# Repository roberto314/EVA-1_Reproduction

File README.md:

# EVA-1_Reproduction

Recreation of the very rare K-K Systems EVA-1 Display Adapter for the Epson HX-20 Computer

In the folder disassembly are three versions of the original firmware:

* eva_orig: original firmware 
* eva_enh: enhanced firmware (mostly original)
* eva_ext: extended firmware (8k Text RAM, additional functions)
    - see the .asm file for more comments.

The gal folder contains the equations and .jed file for the GAL.

The monitor folder contains a modified version of Daniel Tufvesson's monitor. This is just for testing.

In the rom folder one can find the original rom and the font rom.

The schematics folder contains different versions of the reverse engineering process.

* EVA1: the original reverse engineered schematic and board (NOT FOR PRODUCTION!)
* EVA1_production: the mostly original EVA1 for production (DRAM does NOT work!)
* EVA86-2: from sources on the internet redrawn schematics of the EVA86 (not complete!)
* EVA1_v2: new version with SRAM as Graphic RAM, Arduino as mass storage and RP2040 for VGA Output.
* EVA1_Frontplatte: a drill template for the Strapubox 5003 case

For the newest Hardware Revision (0.5) use the File "disassembly/eva_ext/rom.bin" for a 28C64 or 27C64 ROM.

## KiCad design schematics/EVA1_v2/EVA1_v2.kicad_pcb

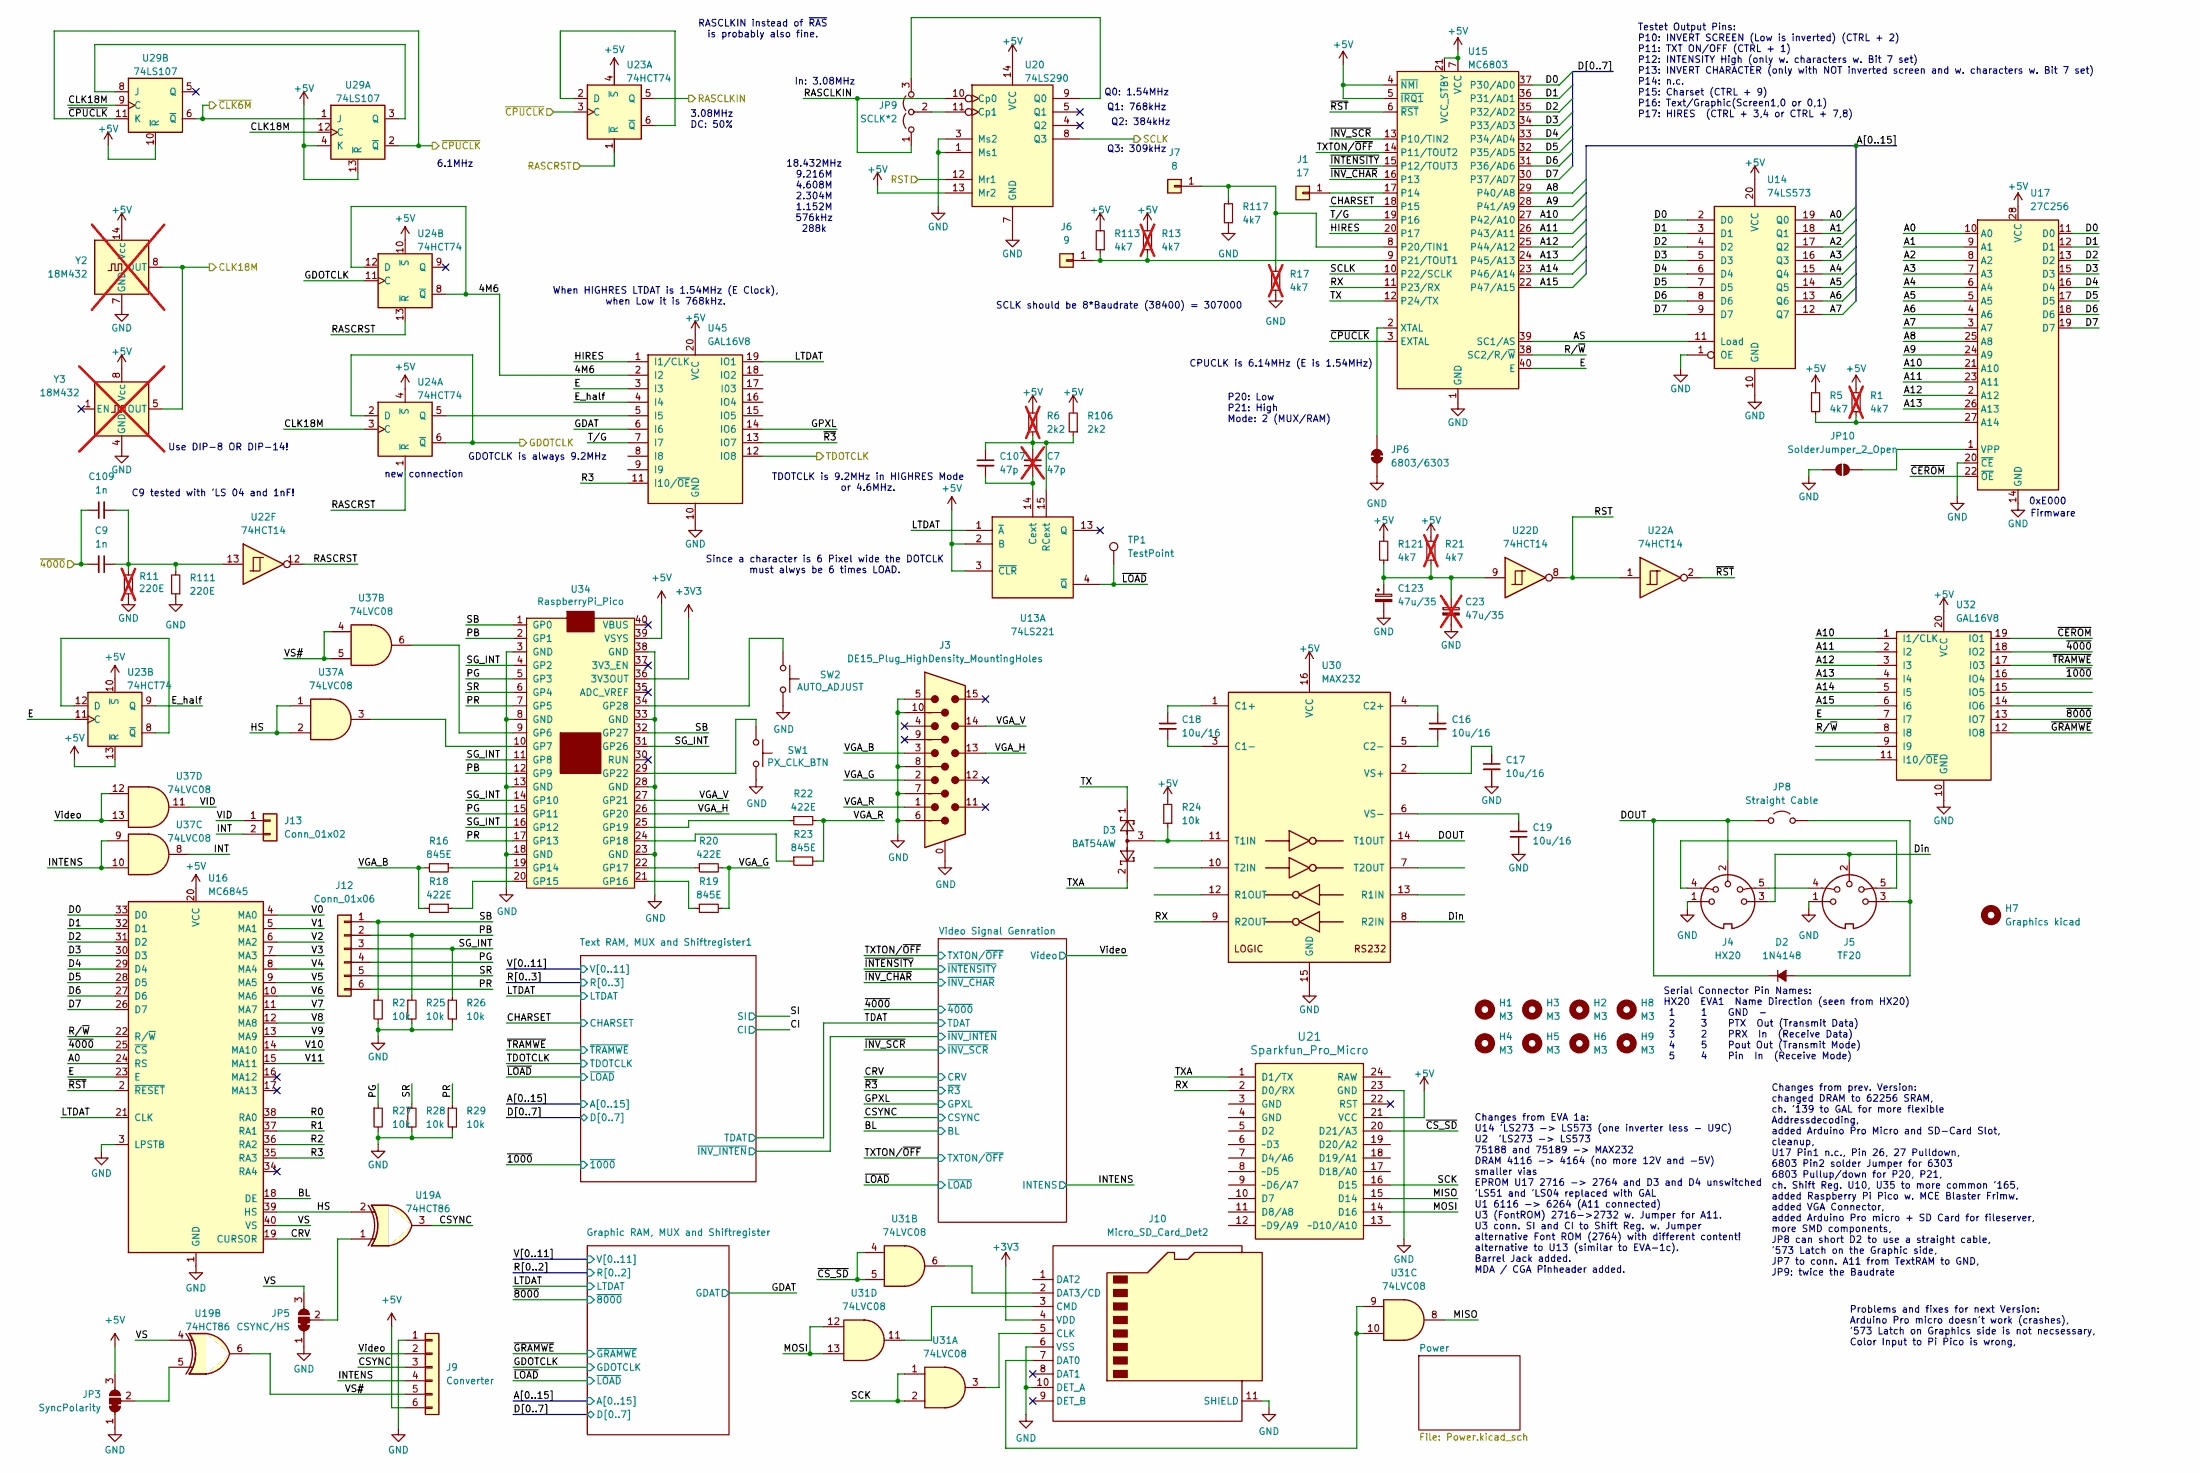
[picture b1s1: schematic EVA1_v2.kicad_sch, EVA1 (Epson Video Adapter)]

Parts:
C7: 47p; C_Disc_D4.7mm_W2.5mm_P5.00mm; not fitted
C9: 1n; C_Disc_D4.7mm_W2.5mm_P5.00mm
C16, C17, C18, C19: 10u/16; CP_Radial_D6.3mm_P2.50mm
C23: 47u/35; CP_Radial_D5.0mm_P2.50mm; not fitted
C107: 47p; C_1206_3216Metric_Pad1.33x1.80mm_HandSolder
C109: 1n; C_1206_3216Metric_Pad1.33x1.80mm_HandSolder
C123: 47u/35; CP_EIA-7343-31_Kemet-D_Pad2.25x2.55mm_HandSolder
D2: 1N4148; D_A-405_P7.62mm_Horizontal
D3: BAT54AW; SOT-23_Handsoldering
H1, H2, H3, H4, H5, H6, H8, H9: M3; MountingHole_3.2mm_M3
H7: Graphics kicad; KiCad-Logo2_6mm_SilkScreen
J1: 17; PinSocket_1x01_P2.54mm_Vertical
J3: DE15_Plug_HighDensity_MountingHoles; DSUB-15-HD_Female_Horizontal_P2.29x1.90mm_EdgePinOffset3.03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
J4: HX20; DIN-5_Stereo
J5: TF20; DIN-5_Stereo
J6: 9; PinSocket_1x01_P2.54mm_Vertical
J7: 8; PinSocket_1x01_P2.54mm_Vertical
J9: Converter; PinHeader_1x06_P2.54mm_Vertical
J10: Micro_SD_Card_Det2; microSD_HC_Hirose_DM3D-SF
J12: Conn_01x06; PinSocket_1x06_P2.54mm_Vertical
J13: Conn_01x02; PinSocket_1x02_P2.54mm_Vertical
JP3: SyncPolarity; SolderJumper-3_P1.3mm_Bridged12_RoundedPad1.0x1.5mm
JP5: CSYNC/HS; SolderJumper-3_P1.3mm_Bridged12_RoundedPad1.0x1.5mm
JP6: 6803/6303; SolderJumper-2_P1.3mm_Bridged_RoundedPad1.0x1.5mm
JP8: Straight Cable; PinHeader_1x02_P2.54mm_Vertical
JP9: SCLK*2; PinHeader_1x03_P2.54mm_Vertical
JP10: SolderJumper_2_Open; SolderJumper-2_P1.3mm_Open_RoundedPad1.0x1.5mm
R1, R13, R17, R21: 4k7; R_Axial_DIN0411_L9.9mm_D3.6mm_P12.70mm_Horizontal; not fitted
R2, R24, R25, R26, R27, R28, R29: 10k; R_1206_3216Metric_Pad1.30x1.75mm_HandSolder
R5, R113, R117, R121: 4k7; R_1206_3216Metric_Pad1.30x1.75mm_HandSolder
R6: 2k2; R_Axial_DIN0411_L9.9mm_D3.6mm_P12.70mm_Horizontal; not fitted
R11: 220E; R_Axial_DIN0411_L9.9mm_D3.6mm_P12.70mm_Horizontal; not fitted
R16, R19, R23: 845E; R_1206_3216Metric_Pad1.30x1.75mm_HandSolder
R18, R20, R22: 422E; R_1206_3216Metric_Pad1.30x1.75mm_HandSolder
R106: 2k2; R_1206_3216Metric_Pad1.30x1.75mm_HandSolder
R111: 220E; R_1206_3216Metric_Pad1.30x1.75mm_HandSolder
SW1: PX_CLK_BTN; SW_Tactile_SPST_Angled_PTS645Vx83-2LFS
SW2: AUTO_ADJUST; SW_Tactile_SPST_Angled_PTS645Vx83-2LFS
TP1: TestPoint; TestPoint_Loop_D1.80mm_Drill1.0mm_Beaded
U13: 74LS221; DIP-16_W7.62mm
U14: 74LS573; DIP-20_W7.62mm
U15: MC6803; DIP-40_W15.24mm_Socket
U16: MC6845; DIP-40_W15.24mm_Socket
U17: 27C256; DIP-28_W15.24mm
U19: 74HCT86; DIP-14_W7.62mm
U20: 74LS290; DIP-14_W7.62mm
U21: Sparkfun_Pro_Micro
U22: 74HCT14; DIP-14_W7.62mm
U23, U24: 74HCT74; DIP-14_W7.62mm
U29: 74LS107; DIP-14_W7.62mm
U30: MAX232; DIP-16_W7.62mm_Socket
U31, U37: 74LVC08; SOIC-14_3.9x8.7mm_P1.27mm
U32, U45: GAL16V8; DIP-20_W7.62mm
U34: RaspberryPi_Pico; raspberry_pi_pico
Y2: 18M432; Oscillator_DIP-14; not fitted
Y3: 18M432; Oscillator_DIP-8; not fitted

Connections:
+3V3: J10.4 (VDD), U34.36 (3V3OUT); also elsewhere on the board
+5V: J9.6, JP3.3 (B), R1.1, R5.1, R6.2, R13.2, R21.2, R24.2, R106.2, R113.2, R121.2, U13.2 (B), U13.3 (~CLR), U14.20 (VCC), U15.4 (~NMI), U15.5 (~IRQ1), U15.7 (VCC), U15.21 (VCC_STBY), U16.20 (VCC), U17.28 (VCC), U20.13 (Mr2), U20.14 (VCC), U21.21 (VCC), U23.4 (~S), U23.10 (~S), U23.13 (~R), U24.4 (~S), U24.10 (~S), U29.4 (K), U29.10 (~R), U29.13 (~R), U30.16 (VCC), U32.20 (VCC), U34.39 (VSYS), U45.20 (VCC), Y2.14 (Vcc), Y3.8 (Vcc); also elsewhere on the board
/4M6: U24.8 (~Q), U24.12 (D), U45.2 (I2)
/A0: U14.19 (Q0), U16.24 (RS), U17.10 (A0); also elsewhere on the board
/A1: U14.18 (Q1), U17.9 (A1); also elsewhere on the board
/A2: U14.17 (Q2), U17.8 (A2); also elsewhere on the board
/A3: U14.16 (Q3), U17.7 (A3); also elsewhere on the board
/A4: U14.15 (Q4), U17.6 (A4); also elsewhere on the board
/A5: U14.14 (Q5), U17.5 (A5); also elsewhere on the board
/A6: U14.13 (Q6), U17.4 (A6); also elsewhere on the board
/A7: U14.12 (Q7), U17.3 (A7); also elsewhere on the board
/A8: U15.29 (P40/A8), U17.25 (A8); also elsewhere on the board
/A9: U15.28 (P41/A9), U17.24 (A9); also elsewhere on the board
/A10: U15.27 (P42/A10), U17.21 (A10), U32.1 (I1/CLK); also elsewhere on the board
/A11: U15.26 (P43/A11), U17.23 (A11), U32.2 (I2); also elsewhere on the board
/A12: U15.25 (P44/A12), U17.2 (A12), U32.3 (I3); also elsewhere on the board
/A13: U15.24 (P45/A13), U17.26 (A13), U32.4 (I4); also elsewhere on the board
/A14: U15.23 (P46/A14), U32.5 (I5); also elsewhere on the board
/A15: U15.22 (P47/A15), U32.6 (I6)
/AS: U14.11 (Load), U15.39 (SC1/AS)
/BL: U16.18 (DE); also elsewhere on the board
/CHARSET: U15.18 (P15); also elsewhere on the board
/CLK18M: U24.3 (C), U29.9 (C), U29.12 (C), Y2.8 (OUT), Y3.5 (OUT)
/CRV: U16.19 (CURSOR); also elsewhere on the board
/CSYNC: J9.3, U19.3; also elsewhere on the board
/D0: U14.2 (D0), U15.37 (P30/AD0), U16.33 (D0), U17.11 (D0); also elsewhere on the board
/D1: U14.3 (D1), U15.36 (P31/AD1), U16.32 (D1), U17.12 (D1); also elsewhere on the board
/D2: U14.4 (D2), U15.35 (P32/AD2), U16.31 (D2), U17.13 (D2); also elsewhere on the board
/D3: U14.5 (D3), U15.34 (P33/AD3), U16.30 (D3), U17.15 (D3); also elsewhere on the board
/D4: U14.6 (D4), U15.33 (P34/AD4), U16.29 (D4), U17.16 (D4); also elsewhere on the board
/D5: U14.7 (D5), U15.32 (P35/AD5), U16.28 (D5), U17.17 (D5); also elsewhere on the board
/D6: U14.8 (D6), U15.31 (P36/AD6), U16.27 (D6), U17.18 (D6); also elsewhere on the board
/D7: U14.9 (D7), U15.30 (P37/AD7), U16.26 (D7), U17.19 (D7); also elsewhere on the board
/DOUT: D2.1 (K), J4.2, JP8.1 (A), U30.14 (T1OUT)
/Din: J4.3, J5.2, U30.8 (R2IN)
/E: U15.40 (E), U16.23 (E), U23.11 (C), U32.7 (I7), U45.3 (I3)
/E_half: U23.9 (Q), U45.4 (I4)
/GDAT: U45.6 (I6); also elsewhere on the board
/GDOTCLK: U24.2 (D), U24.6 (~Q), U24.11 (C); also elsewhere on the board
/GPXL: U45.14 (IO6); also elsewhere on the board
/HIRES: U15.20 (P17), U45.1 (I1/CLK)
/HS: U16.39 (HS), U19.2, U37.1, U37.2
/INT: J13.2, U37.8
/INTENS: J9.4, U37.9, U37.10; also elsewhere on the board
/LTDAT: U13.1 (~A), U16.21 (CLK), U45.19 (IO1); also elsewhere on the board
/MISO: U21.15 (D14), U31.8
/MOSI: U21.14 (D16), U31.12, U31.13
/PB: J12.2, R25.1, U34.2 (GP1), U34.12 (GP9)
/PG: J12.4, R27.1, U34.5 (GP3), U34.15 (GP11)
/PR: J12.6, R29.1, U34.7 (GP5), U34.17 (GP13)
/R0: U16.38 (RA0); also elsewhere on the board
/R1: U16.37 (RA1); also elsewhere on the board
/R2: U16.36 (RA2); also elsewhere on the board
/R3: U16.35 (RA3), U45.11 (I10/~OE); also elsewhere on the board
/RASCLKIN: JP9.1 (A), U20.10 (Cp0), U23.5 (Q)
/RASCRST: U22.12, U23.1 (~R), U24.1 (~R), U24.13 (~R)
/RST: U20.12 (Mr1), U22.1, U22.8
/RX: U15.11 (P23/RX), U21.2 (D0/RX), U30.9 (R2OUT)
/R/~W: U15.38 (SC2/R/~W), U16.22 (R/~W), U32.8 (I8)
/SB: J12.1, R2.1, U34.1 (GP0), U34.32 (GP27)
/SCK: U21.16 (D15), U31.1, U31.2
/SCLK: U15.10 (P22/SCLK), U20.8 (Q3)
/SG_INT: J12.3, R26.1, U34.4 (GP2), U34.11 (GP8), U34.14 (GP10), U34.16 (GP12), U34.31 (GP26)
/SR: J12.5, R28.1, U34.6 (GP4)
/TDOTCLK: U45.12 (IO8); also elsewhere on the board
/TX: D3.1, U15.12 (P24/TX)
/TXA: D3.2, U21.1 (D1/TX)
/TXTON/~OFF: U15.14 (P11/TOUT2); also elsewhere on the board
/V0: U16.4 (MA0); also elsewhere on the board
/V1: U16.5 (MA1); also elsewhere on the board
/V2: U16.6 (MA2); also elsewhere on the board
/V3: U16.7 (MA3); also elsewhere on the board
/V4: U16.8 (MA4); also elsewhere on the board
/V5: U16.9 (MA5); also elsewhere on the board
/V6: U16.10 (MA6); also elsewhere on the board
/V7: U16.11 (MA7); also elsewhere on the board
/V8: U16.12 (MA8); also elsewhere on the board
/V9: U16.13 (MA9); also elsewhere on the board
/V10: U16.14 (MA10); also elsewhere on the board
/V11: U16.15 (MA11); also elsewhere on the board
/VGA_B: J3.3, R16.2, R18.2
/VGA_G: J3.2, R19.2, R20.2
/VGA_H: J3.13, U34.26 (GP20)
/VGA_R: J3.1, R22.2, R23.2
/VGA_V: J3.14, U34.27 (GP21)
/VID: J13.1, U37.11
/VS: JP5.3 (B), U16.40 (VS), U19.4
/VS#: J9.5, U19.6, U37.4, U37.5
/Video: J9.2, U37.12, U37.13; also elsewhere on the board
/~1000: U32.16 (IO4); also elsewhere on the board
/~4000: C9.2, C109.1, U16.25 (~CS), U32.18 (IO2)
/~8000: U32.13 (IO7); also elsewhere on the board
/~CEROM: U17.22 (~OE), U32.19 (IO1)
/~CLK6M: U29.1 (J), U29.6 (~Q)
/~CPUCLK: U15.3 (EXTAL), U23.3 (C), U29.2 (~Q), U29.11 (K)
/~CS_SD: U21.20 (D21/A3), U31.4, U31.5
/~GRAMWE: U32.12 (IO8); also elsewhere on the board
/~INTENSITY: U15.15 (P12/TOUT3); also elsewhere on the board
/~INV_CHAR: U15.16 (P13); also elsewhere on the board
/~INV_SCR: U15.13 (P10/TIN2); also elsewhere on the board
/~LOAD: TP1.1, U13.4 (~Q); also elsewhere on the board
/~R3: U45.13 (IO7); also elsewhere on the board
/~RST: U15.6 (~RST), U16.2 (~RESET), U22.2
/~TRAMWE: U32.17 (I03); also elsewhere on the board
GND: C17.2, C19.2, C23.2, C123.2, J3.0, J3.5, J3.6, J3.7, J3.8, J3.10, J4.1, J5.1, J9.1, J10.6 (VSS), J10.10 (DET_A), J10.11 (SHIELD), JP3.1 (A), JP5.1 (A), JP6.1 (A), JP10.1 (A), R2.2, R11.1, R17.1, R25.2, R26.2, R27.2, R28.2, R29.2, R111.1, R117.1, SW1.2, SW2.2, U14.1 (OE), U14.10 (GND), U15.1 (GND), U16.1 (GND), U16.3 (LPSTB), U17.14 (GND), U17.20 (~CE), U20.1 (Ms1), U20.3 (Ms2), U20.7 (GND), U21.23 (GND), U30.15 (GND), U32.10 (GND), U34.3 (GND), U34.8 (GND), U34.13 (GND), U34.18 (GND), U34.23 (GND), U34.28 (GND), U34.33 (GND), U34.38 (GND), U45.10 (GND), Y2.7 (GND), Y3.4 (GND); also elsewhere on the board
unnamed: C9.1, C109.2, R11.2, R111.2, U22.13
unnamed: C23.1, C123.1, R21.1, R121.1, U22.9
unnamed: D2.2 (A), J5.3, JP8.2 (B)
unnamed: J1.1, U15.17 (P14)
unnamed: J4.4, J5.5
unnamed: J4.5, J5.4
unnamed: J6.1, R13.1, R113.1, U15.9 (P21/TOUT1)
unnamed: J7.1, R17.2, R117.2, U15.8 (P20/TIN1)
unnamed: J10.5 (CLK), U31.3
unnamed: J10.3 (CMD), U31.11
unnamed: J10.7 (DAT0), U31.9, U31.10
unnamed: J10.2 (DAT3/CD), U31.6
unnamed: JP3.2 (C), U19.5
unnamed: JP5.2 (C), U19.1
unnamed: JP6.2 (B), U15.2 (XTAL)
unnamed: JP9.3 (B), U20.9 (Q0)
unnamed: JP9.2 (C), U20.11 (Cp1)
unnamed: JP10.2 (B), U17.1 (VPP)
unnamed: C7.1, C107.2, U13.14 (Cext)
unnamed: C7.2, C107.1, R6.1, R106.1, U13.15 (RCext)
unnamed: R1.2, R5.2, U17.27 (A14)
unnamed: U23.2 (D), U23.6 (~Q)
unnamed: U23.8 (~Q), U23.12 (D)
unnamed: U24.5 (Q), U45.5 (I5)
unnamed: U29.3 (Q), U29.8 (J)
unnamed: C18.1, U30.1 (C1+)
unnamed: C18.2, U30.3 (C1-)
unnamed: C16.1, U30.4 (C2+)
unnamed: C16.2, U30.5 (C2-)
unnamed: D3.3, R24.1, U30.11 (T1IN)
unnamed: C17.1, U30.2 (VS+)
unnamed: C19.1, U30.6 (VS-)
unnamed: U34.9 (GP6), U37.6
unnamed: U34.10 (GP7), U37.3
unnamed: R16.1, U34.19 (GP14)
unnamed: R18.1, U34.20 (GP15)
unnamed: R19.1, U34.21 (GP16)
unnamed: R20.1, U34.22 (GP17)
unnamed: R23.1, U34.24 (GP18)
unnamed: R22.1, U34.25 (GP19)
unnamed: SW1.1, U34.29 (GP22)
unnamed: SW2.1, U34.34 (GP28)

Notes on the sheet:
P20: Low P21: High Mode: 2 (MUX/RAM)
3.08MHz DC: 50%
TDOTCLK is 9.2MHz in HIGHRES Mode or 4.6MHz.
Testet Output Pins: P10: INVERT SCREEN (Low is inverted) (CTRL + 2) P11: TXT ON/OFF (CTRL + 1) P12: INTENSITY High (only w. characters w. Bit 7 set) P13: INVERT CHARACTER (only with NOT inverted screen and w. characters w. Bit 7 set) P14: n.c. P15: Charset (CTRL + 9) P16: Text/Graphic(Screen1,0 or 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
RASCLKIN instead of ~{RAS} is probably also fine.
Use DIP-8 OR DIP-14!
GDOTCLK is always 9.2MHz
C9 tested with 'LS 04 and 1nF!
Q1: 768kHz
CPUCLK is 6.14MHz (E is 1.54MHz)
Serial Connector Pin Names: HX20 EVA1 Name Direction (seen from HX20) 1 1 GND - 2 3 PTX Out (Transmit Data) 3 2 PRX In (Receive Data) 4 5 Pout Out (Transmit Mode) 5 4 Pin In (Receive Mode)
Q3: 309kHz
Changes from EVA 1a: U14 'LS273 -> LS573 (one inverter less - U9C) U2 'LS273 -> LS573 75188 and 75189 -> MAX232 DRAM 4116 -> 4164 (no more 12V and -5V) smaller vias EPROM U17 2716 -> 2764 and D3 and D4 unswitched 'LS51 and 'LS04 replaced with GAL U1 6116 -> 6264 (A11 connected) U3 (FontROM) 2716->2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
SCLK should be 8*Baudrate (38400) = 307000
When HIGHRES LTDAT is 1.54MHz (E Clock), when Low it is 768kHz.
6.1MHz
Since a character is 6 Pixel wide the DOTCLK must alwys be 6 times LOAD.
Firmware
18.432MHz 9.216M 4.608M 2.304M 1.152M 576kHz 288k
new connection
0xE000
Q0: 1.54MHz
In: 3.08MHz
Q2: 384kHz
Changes from prev. Version: changed DRAM to 62256 SRAM, ch. '139 to GAL for more flexible Addressdecoding, added Arduino Pro Micro and SD-Card Slot, cleanup, U17 Pin1 n.c., Pin 26, 27 Pulldown, 6803 Pin2 solder Jumper for 6303 6803 Pullup/down for P20, P21, ch. Shift Reg. U10, U35 to more common '1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
Problems and fixes for next Version: Arduino Pro micro doesn't work (crashes), '573 Latch on Graphics side is not necsessary, Color Input to Pi Pico is wrong,

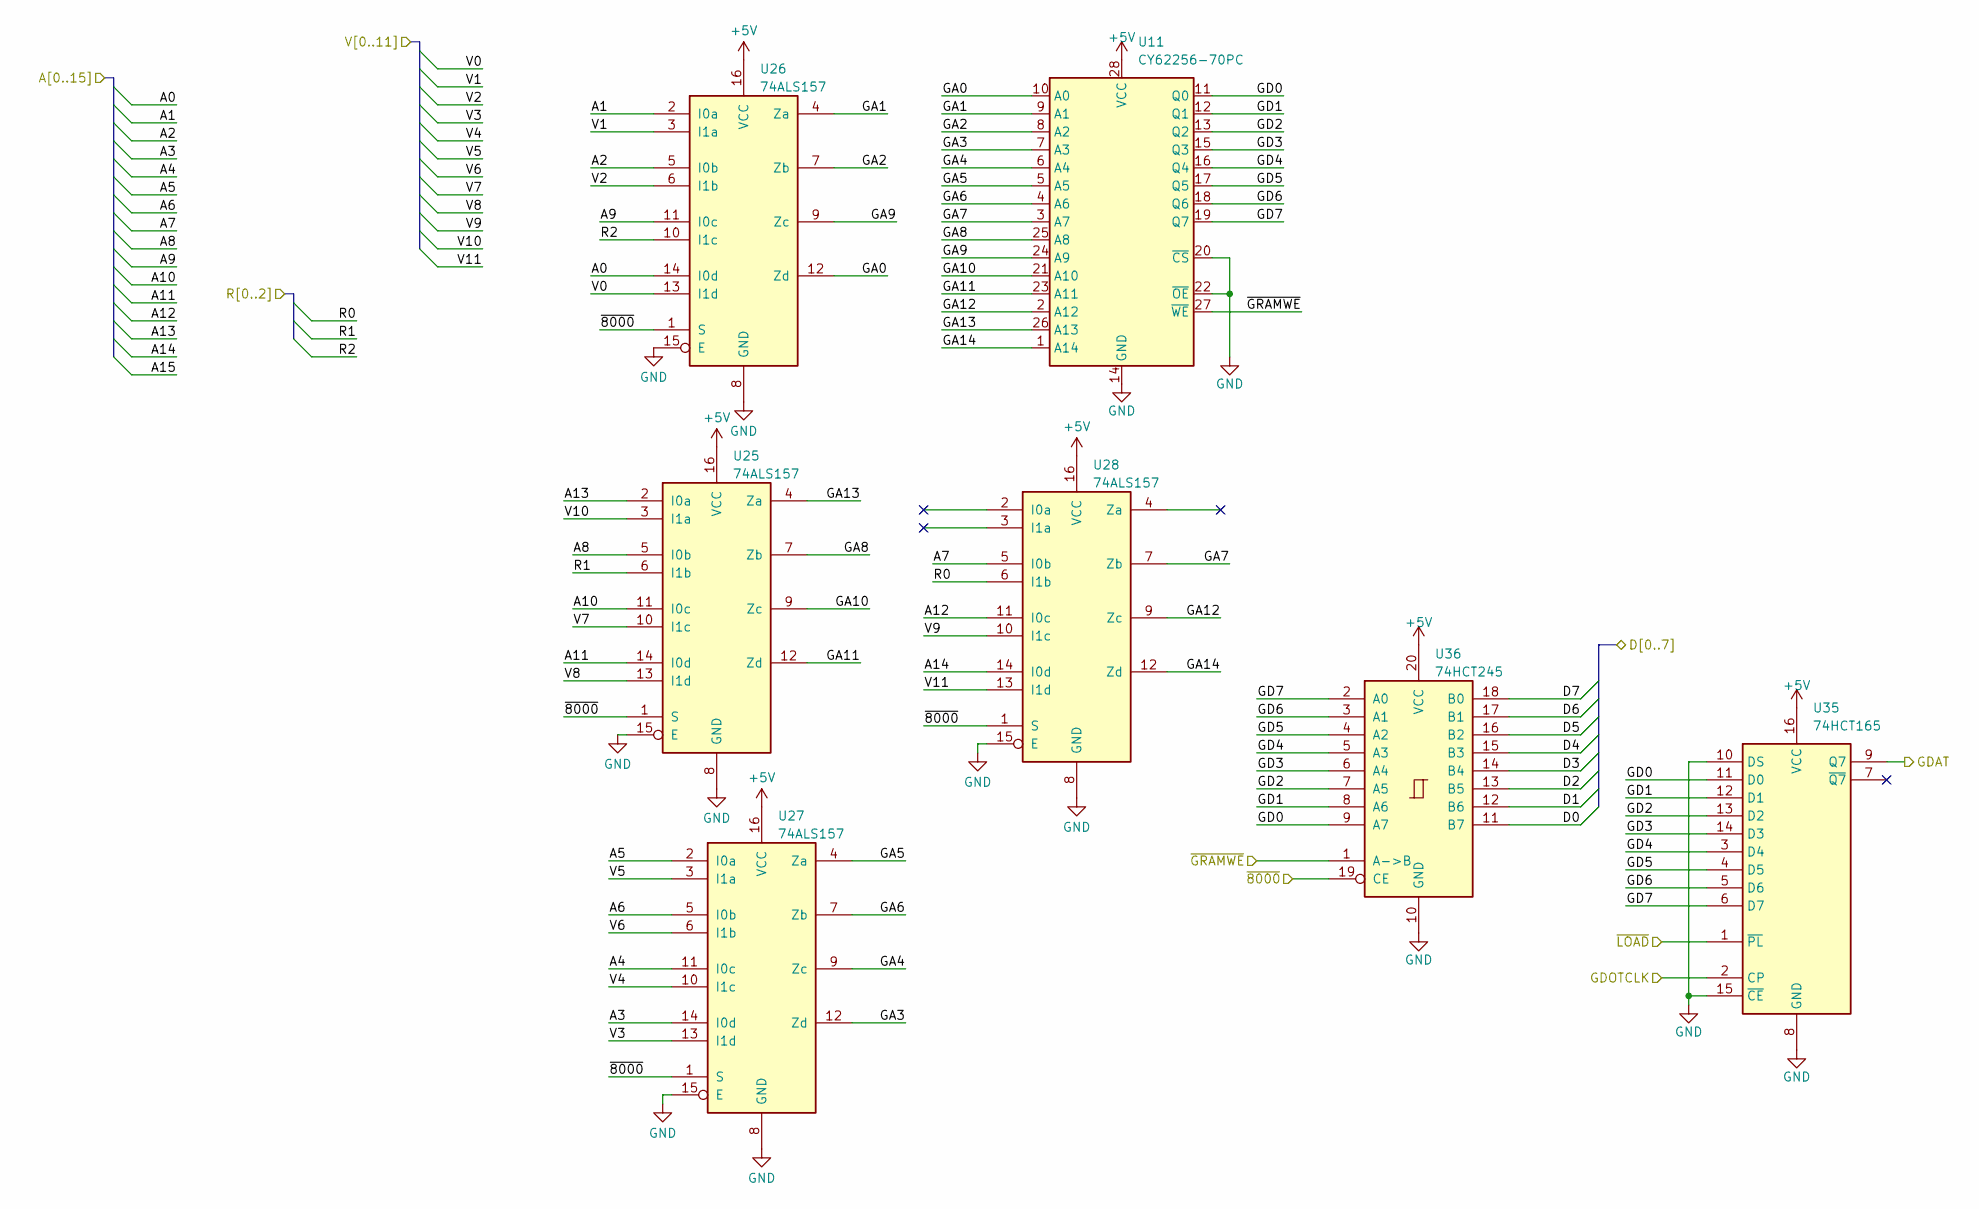
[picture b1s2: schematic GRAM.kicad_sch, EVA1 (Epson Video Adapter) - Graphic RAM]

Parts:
U11: CY62256-70PC; DIP-28_W15.24mm
U25, U26, U27, U28: 74ALS157; DIP-16_W7.62mm
U35: 74HCT165; DIP-16_W7.62mm_Socket
U36: 74HCT245; DIP-20_W7.62mm

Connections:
+5V: U11.28 (VCC), U25.16 (VCC), U26.16 (VCC), U27.16 (VCC), U28.16 (VCC), U35.16 (VCC), U36.20 (VCC); also elsewhere on the board
/A0: U26.14 (I0d); also elsewhere on the board
/A1: U26.2 (I0a); also elsewhere on the board
/A2: U26.5 (I0b); also elsewhere on the board
/A3: U27.14 (I0d); also elsewhere on the board
/A4: U27.11 (I0c); also elsewhere on the board
/A5: U27.2 (I0a); also elsewhere on the board
/A6: U27.5 (I0b); also elsewhere on the board
/A7: U28.5 (I0b); also elsewhere on the board
/A8: U25.5 (I0b); also elsewhere on the board
/A9: U26.11 (I0c); also elsewhere on the board
/A10: U25.11 (I0c); also elsewhere on the board
/A11: U25.14 (I0d); also elsewhere on the board
/A12: U28.11 (I0c); also elsewhere on the board
/A13: U25.2 (I0a); also elsewhere on the board
/A14: U28.14 (I0d); also elsewhere on the board
/D0: U36.11 (B7); also elsewhere on the board
/D1: U36.12 (B6); also elsewhere on the board
/D2: U36.13 (B5); also elsewhere on the board
/D3: U36.14 (B4); also elsewhere on the board
/D4: U36.15 (B3); also elsewhere on the board
/D5: U36.16 (B2); also elsewhere on the board
/D6: U36.17 (B1); also elsewhere on the board
/D7: U36.18 (B0); also elsewhere on the board
/GDAT: U35.9 (Q7); also elsewhere on the board
/GDOTCLK: U35.2 (CP); also elsewhere on the board
/Graphic RAM, MUX and Shiftregister/GA0: U11.10 (A0), U26.12 (Zd)
/Graphic RAM, MUX and Shiftregister/GA1: U11.9 (A1), U26.4 (Za)
/Graphic RAM, MUX and Shiftregister/GA2: U11.8 (A2), U26.7 (Zb)
/Graphic RAM, MUX and Shiftregister/GA3: U11.7 (A3), U27.12 (Zd)
/Graphic RAM, MUX and Shiftregister/GA4: U11.6 (A4), U27.9 (Zc)
/Graphic RAM, MUX and Shiftregister/GA5: U11.5 (A5), U27.4 (Za)
/Graphic RAM, MUX and Shiftregister/GA6: U11.4 (A6), U27.7 (Zb)
/Graphic RAM, MUX and Shiftregister/GA7: U11.3 (A7), U28.7 (Zb)
/Graphic RAM, MUX and Shiftregister/GA8: U11.25 (A8), U25.7 (Zb)
/Graphic RAM, MUX and Shiftregister/GA9: U11.24 (A9), U26.9 (Zc)
/Graphic RAM, MUX and Shiftregister/GA10: U11.21 (A10), U25.9 (Zc)
/Graphic RAM, MUX and Shiftregister/GA11: U11.23 (A11), U25.12 (Zd)
/Graphic RAM, MUX and Shiftregister/GA12: U11.2 (A12), U28.9 (Zc)
/Graphic RAM, MUX and Shiftregister/GA13: U11.26 (A13), U25.4 (Za)
/Graphic RAM, MUX and Shiftregister/GA14: U11.1 (A14), U28.12 (Zd)
/Graphic RAM, MUX and Shiftregister/GD0: U11.11 (Q0), U35.11 (D0), U36.9 (A7)
/Graphic RAM, MUX and Shiftregister/GD1: U11.12 (Q1), U35.12 (D1), U36.8 (A6)
/Graphic RAM, MUX and Shiftregister/GD2: U11.13 (Q2), U35.13 (D2), U36.7 (A5)
/Graphic RAM, MUX and Shiftregister/GD3: U11.15 (Q3), U35.14 (D3), U36.6 (A4)
/Graphic RAM, MUX and Shiftregister/GD4: U11.16 (Q4), U35.3 (D4), U36.5 (A3)
/Graphic RAM, MUX and Shiftregister/GD5: U11.17 (Q5), U35.4 (D5), U36.4 (A2)
/Graphic RAM, MUX and Shiftregister/GD6: U11.18 (Q6), U35.5 (D6), U36.3 (A1)
/Graphic RAM, MUX and Shiftregister/GD7: U11.19 (Q7), U35.6 (D7), U36.2 (A0)
/R0: U28.6 (I1b); also elsewhere on the board
/R1: U25.6 (I1b); also elsewhere on the board
/R2: U26.10 (I1c); also elsewhere on the board
/V0: U26.13 (I1d); also elsewhere on the board
/V1: U26.3 (I1a); also elsewhere on the board
/V2: U26.6 (I1b); also elsewhere on the board
/V3: U27.13 (I1d); also elsewhere on the board
/V4: U27.10 (I1c); also elsewhere on the board
/V5: U27.3 (I1a); also elsewhere on the board
/V6: U27.6 (I1b); also elsewhere on the board
/V7: U25.10 (I1c); also elsewhere on the board
/V8: U25.13 (I1d); also elsewhere on the board
/V9: U28.10 (I1c); also elsewhere on the board
/V10: U25.3 (I1a); also elsewhere on the board
/V11: U28.13 (I1d); also elsewhere on the board
/~8000: U25.1 (S), U26.1 (S), U27.1 (S), U28.1 (S), U36.19 (CE); also elsewhere on the board
/~GRAMWE: U11.27 (~WE), U36.1 (A->B); also elsewhere on the board
/~LOAD: U35.1 (~PL); also elsewhere on the board
GND: U11.14 (GND), U11.20 (~CS), U11.22 (~OE), U25.8 (GND), U25.15 (E), U26.8 (GND), U26.15 (E), U27.8 (GND), U27.15 (E), U28.8 (GND), U28.15 (E), U35.8 (GND), U35.10 (DS), U35.15 (~CE), U36.10 (GND); also elsewhere on the board

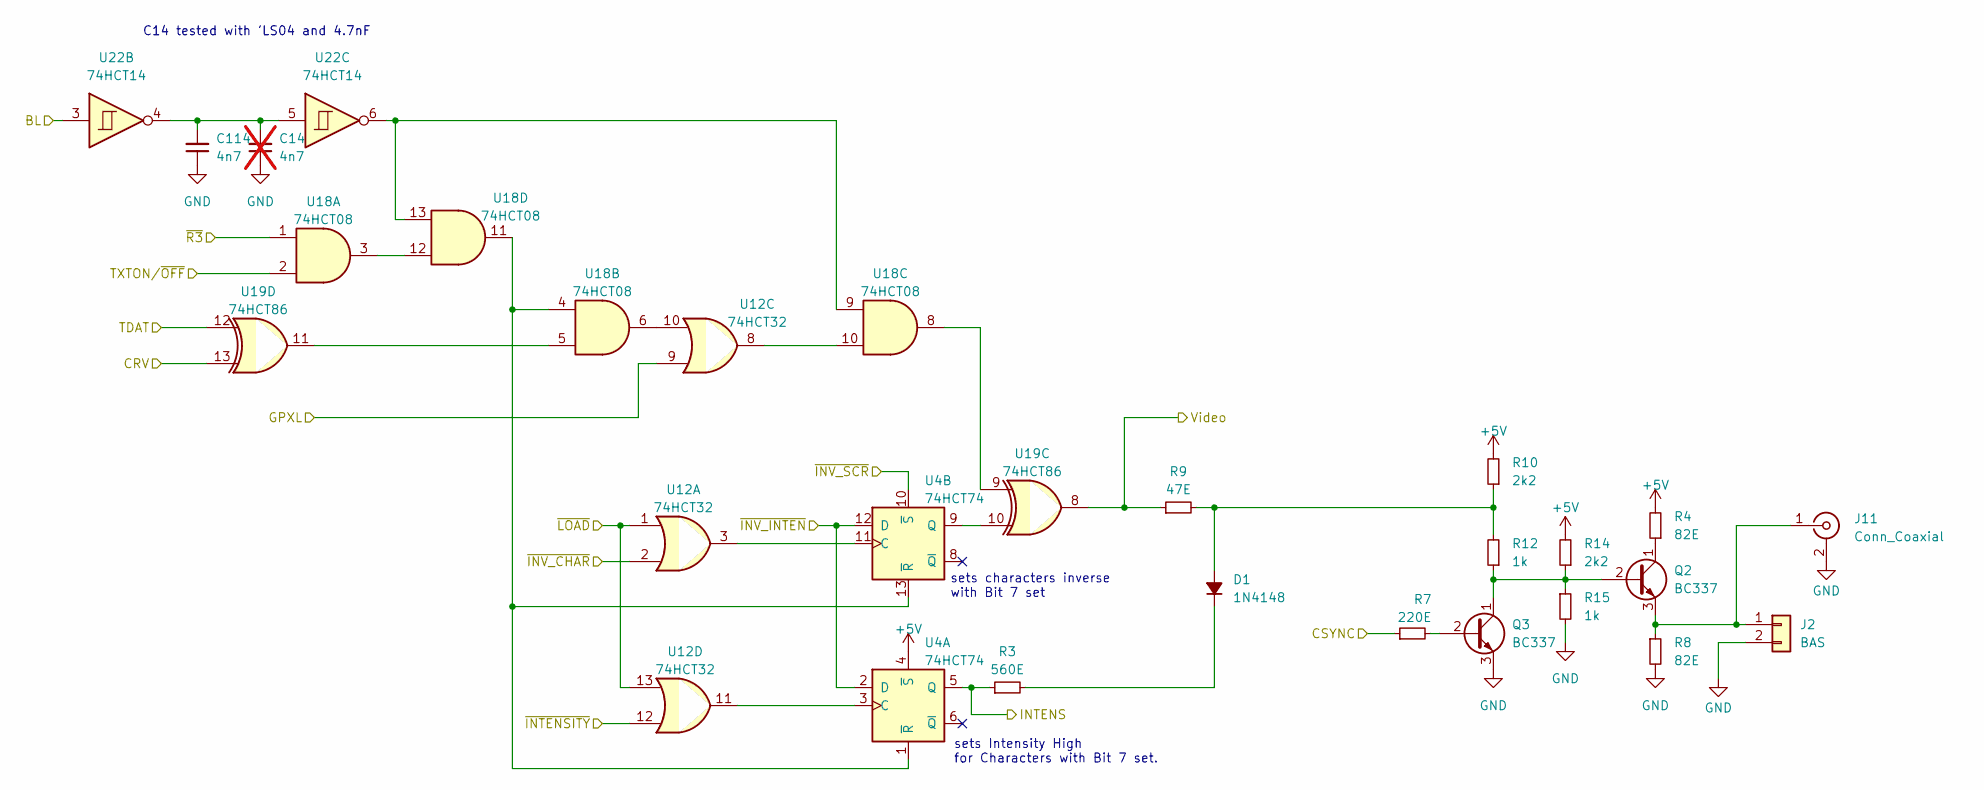
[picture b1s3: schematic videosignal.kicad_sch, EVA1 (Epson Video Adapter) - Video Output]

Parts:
C14: 4n7; C_Disc_D4.7mm_W2.5mm_P5.00mm; not fitted
C114: 4n7; C_1206_3216Metric_Pad1.33x1.80mm_HandSolder
D1: 1N4148; D_A-405_P7.62mm_Horizontal
J2: BAS; PinHeader_1x02_P2.54mm_Vertical
J11: Conn_Coaxial; Keystone_RCA-Jack
Q2, Q3: BC337; TO-92_Wide
R3: 560E; R_Axial_DIN0411_L9.9mm_D3.6mm_P12.70mm_Horizontal
R4, R8: 82E; R_Axial_DIN0411_L9.9mm_D3.6mm_P12.70mm_Horizontal
R7: 220E; R_Axial_DIN0411_L9.9mm_D3.6mm_P12.70mm_Horizontal
R9: 47E; R_Axial_DIN0411_L9.9mm_D3.6mm_P12.70mm_Horizontal
R10, R14: 2k2; R_Axial_DIN0411_L9.9mm_D3.6mm_P12.70mm_Horizontal
R12, R15: 1k; R_Axial_DIN0411_L9.9mm_D3.6mm_P12.70mm_Horizontal
U4: 74HCT74; DIP-14_W7.62mm
U12: 74HCT32; DIP-14_W7.62mm
U18: 74HCT08; DIP-14_W7.62mm
U19: 74HCT86; DIP-14_W7.62mm
U22: 74HCT14; DIP-14_W7.62mm

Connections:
+5V: R4.2, R10.2, R14.2, U4.4 (~S); also elsewhere on the board
/BL: U22.3; also elsewhere on the board
/CRV: U19.13; also elsewhere on the board
/CSYNC: R7.1; also elsewhere on the board
/GPXL: U12.9; also elsewhere on the board
/INTENS: R3.1, U4.5 (Q); also elsewhere on the board
/TDAT: U19.12; also elsewhere on the board
/TXTON/~OFF: U18.2; also elsewhere on the board
/Text RAM, MUX and Shiftregister1/~INV_INTEN: U4.2 (D), U4.12 (D); also elsewhere on the board
/Video: R9.1, U19.8; also elsewhere on the board
/~INTENSITY: U12.12; also elsewhere on the board
/~INV_CHAR: U12.2; also elsewhere on the board
/~INV_SCR: U4.10 (~S); also elsewhere on the board
/~LOAD: U12.1, U12.13; also elsewhere on the board
/~R3: U18.1; also elsewhere on the board
GND: C14.1, C114.1, J2.2, J11.2 (Ext), Q3.3 (E), R8.2, R15.2; also elsewhere on the board
unnamed: C14.2, C114.2, U22.4, U22.5
unnamed: D1.2 (A), R9.2, R10.1, R12.2
unnamed: D1.1 (K), R3.2
unnamed: J2.1, J11.1 (In), Q2.3 (E), R8.1
unnamed: Q2.2 (B), Q3.1 (C), R12.1, R14.1, R15.1
unnamed: Q2.1 (C), R4.1
unnamed: Q3.2 (B), R7.2
unnamed: U4.3 (C), U12.11
unnamed: U4.1 (~R), U4.13 (~R), U18.4, U18.11
unnamed: U4.11 (C), U12.3
unnamed: U4.9 (Q), U19.10
unnamed: U12.8, U18.10
unnamed: U12.10, U18.6
unnamed: U18.5, U19.11
unnamed: U18.8, U19.9
unnamed: U18.3, U18.12
unnamed: U18.9, U18.13, U22.6

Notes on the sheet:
C14 tested with 'LS04 and 4.7nF
sets Intensity High for Characters with Bit 7 set.
sets characters inverse with Bit 7 set

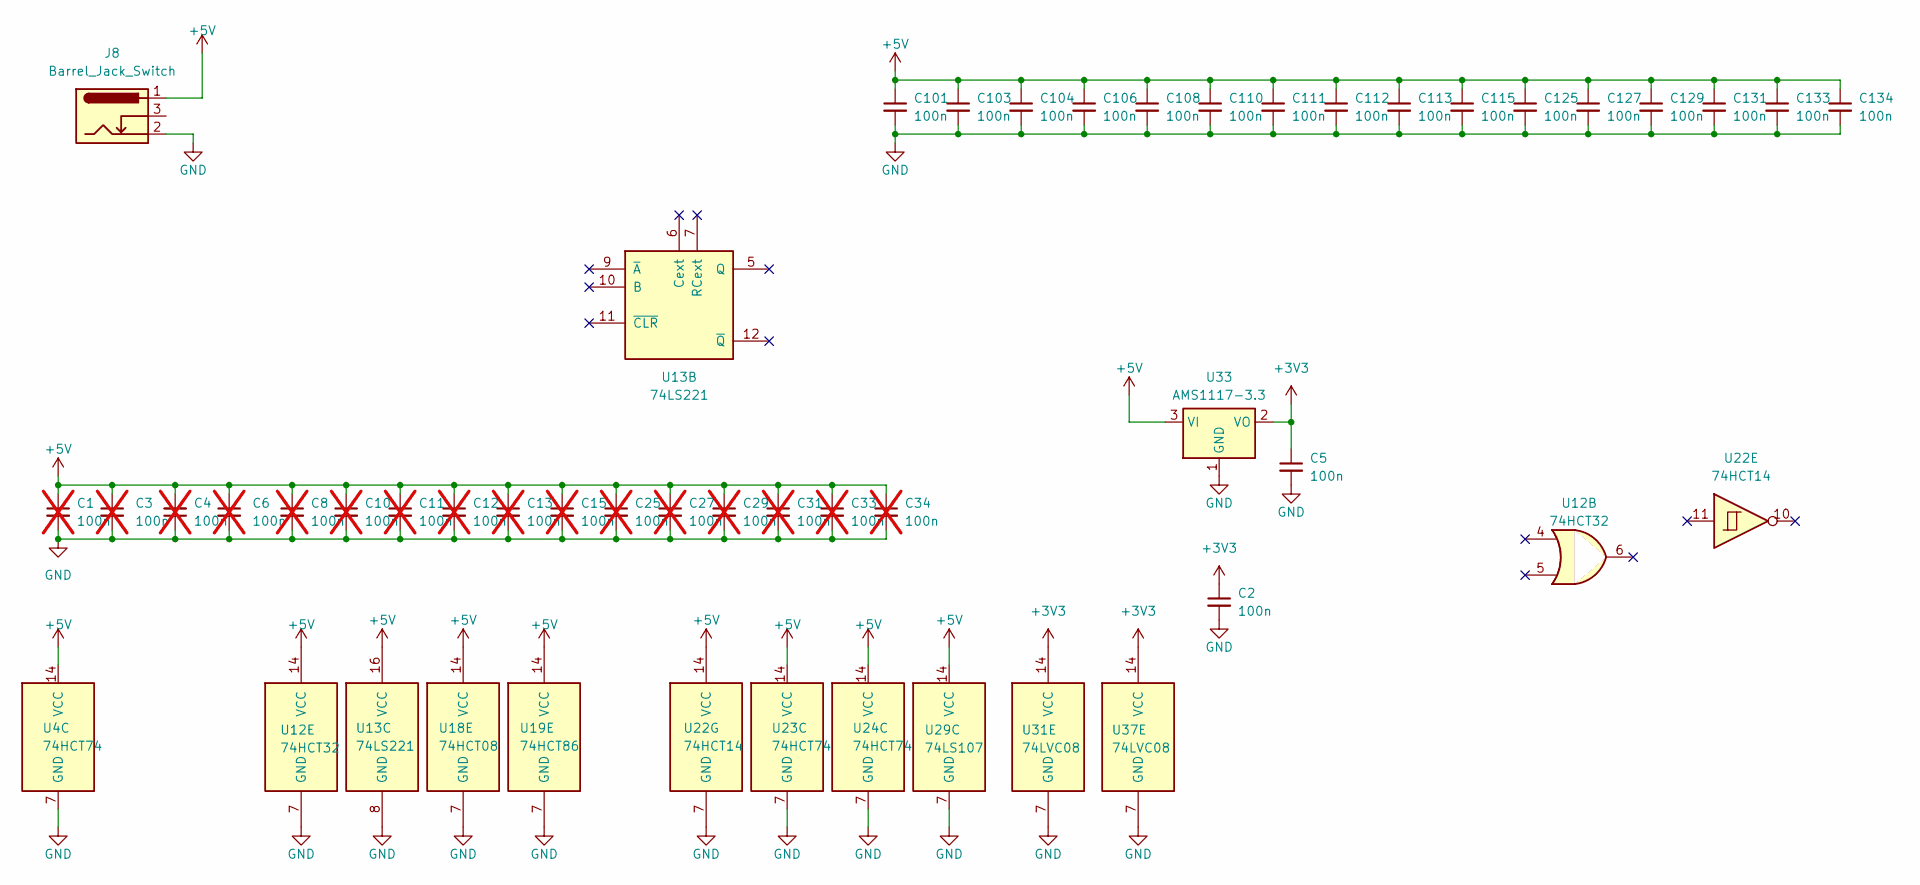
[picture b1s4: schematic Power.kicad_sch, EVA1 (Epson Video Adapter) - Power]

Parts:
C1, C3, C4, C6, C8, C10, C11, C12, C13, C15, C25, C27, C29, C31, C33, C34: 100n; C_Disc_D4.7mm_W2.5mm_P5.00mm; not fitted
C2, C5, C101, C103, C104, C106, C108, C110, C111, C112, C113, C115, C125, C127, C129, C131, C133, C134: 100n; C_1206_3216Metric_Pad1.33x1.80mm_HandSolder
J8: Barrel_Jack_Switch; BarrelJack_Wuerth_6941xx301002
U4, U23, U24: 74HCT74; DIP-14_W7.62mm
U12: 74HCT32; DIP-14_W7.62mm
U13: 74LS221; DIP-16_W7.62mm
U18: 74HCT08; DIP-14_W7.62mm
U19: 74HCT86; DIP-14_W7.62mm
U22: 74HCT14; DIP-14_W7.62mm
U29: 74LS107; DIP-14_W7.62mm
U31, U37: 74LVC08; SOIC-14_3.9x8.7mm_P1.27mm
U33: AMS1117-3.3; SOT-223-3_TabPin2

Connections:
+3V3: C2.1, C5.1, U31.14 (VCC), U33.2 (VO), U37.14 (VCC); also elsewhere on the board
+5V: C1.1, C3.1, C4.2, C6.1, C8.1, C10.1, C11.1, C12.1, C13.1, C15.1, C25.1, C27.1, C29.1, C31.1, C33.1, C34.1, C101.1, C103.1, C104.1, C106.1, C108.1, C110.1, C111.1, C112.1, C113.1, C115.1, C125.1, C127.1, C129.1, C131.1, C133.1, C134.1, J8.1, U4.14 (VCC), U12.14 (VCC), U13.16 (VCC), U18.14 (VCC), U19.14 (VCC), U22.14 (VCC), U23.14 (VCC), U24.14 (VCC), U29.14 (VCC), U33.3 (VI); also elsewhere on the board
GND: C1.2, C2.2, C3.2, C4.1, C5.2, C6.2, C8.2, C10.2, C11.2, C12.2, C13.2, C15.2, C25.2, C27.2, C29.2, C31.2, C33.2, C34.2, C101.2, C103.2, C104.2, C106.2, C108.2, C110.2, C111.2, C112.2, C113.2, C115.2, C125.2, C127.2, C129.2, C131.2, C133.2, C134.2, J8.2, U4.7 (GND), U12.7 (GND), U13.8 (GND), U18.7 (GND), U19.7 (GND), U22.7 (GND), U23.7 (GND), U24.7 (GND), U29.7 (GND), U31.7 (GND), U33.1 (GND), U37.7 (GND); also elsewhere on the board
